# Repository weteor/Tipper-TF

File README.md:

# Tipper-TF
34 keys split unibody BLE keyboard. 

## Features

- low profile
- choc v1 w/ choc spacing
- angled hands
- splayed columns
- variable height on outer colum. Can be adjusted by a combination of pinheaders(1.27mm pitch, 1mm or 1.5mm height) + (at the moment) spacer pcbs.
- 1.54'' epaper display (Good Display GDEW0154M09)
- Bluetooth and USB connection 
- case files are supplied (stl, as well as freecad files)
- ZMK firmware support

## Want one?
All production files you need to build your own Tipper TF can be found [here](https://github.com/weteor/Tipper-TF/tree/main/production).

Please see the [build instruction](https://github.com/weteor/Tipper-TF/tree/main/production/build_instructions.md) for a more detailed listing of all things needed.

All PCBs come with SMT assembly files, so you can order them fully assembled. No need to solder another 50 diodes.

The files for the case are also provided. If you don't own a 3d printer, I've used JLCPCBs printing service (MJF nylon) and it turned out very good, so maybe take a look at that option.

### firmware 
The Tipper TF uses ZMK firmware.

The zmk driver for the display driver chip is not in the official repository yet, so you will have to use [my ZMK fork](https://github.com/weteor/zmk/tree/Tipper_TF_rev2) if you want to build a firmware locally.

If you prefer the github workflow, you can find the zmk config for the Tipper TF [here](https://github.com/weteor/Tipper_TF-Config). The config is already configured to pull ZMK from my fork, so you don't have to do anything further.

### some more pictures

## remarks
MKB keycaps work great on the Tipper, but I very much prefer the Chicago Steno caps by Pseudoku. He provides some nice SCAD files for those, you may find them in [his github](https://github.com/pseudoku/PseudoMakeMeKeyCapProfiles). He also sells them in his shop [www.asymplex.xyz](https://www.asymplex.xyz/).

### thanks for help and inspiration:
- [MangoIV](https://github.com/MangoIV/) and his [le-chiffre-ble](https://github.com/MangoIV/le_chiff_ble)
- [broom's](https://github.com/davidphilipbarr) [hypergolic](https://github.com/davidphilipbarr/hypergolic)
- [marv](https://github.com/MarvFPV) invaluable feedback and help with the case design

## the rest
Everything in this repository is free to use however you might see fit. If you want to support me and my projects, please consider linking back to this repository if you build/change/use anything. 

If you would like to send me a tip, you could do it [here](https://ko-fi.com/weteor) (Please don't feel like you have to).

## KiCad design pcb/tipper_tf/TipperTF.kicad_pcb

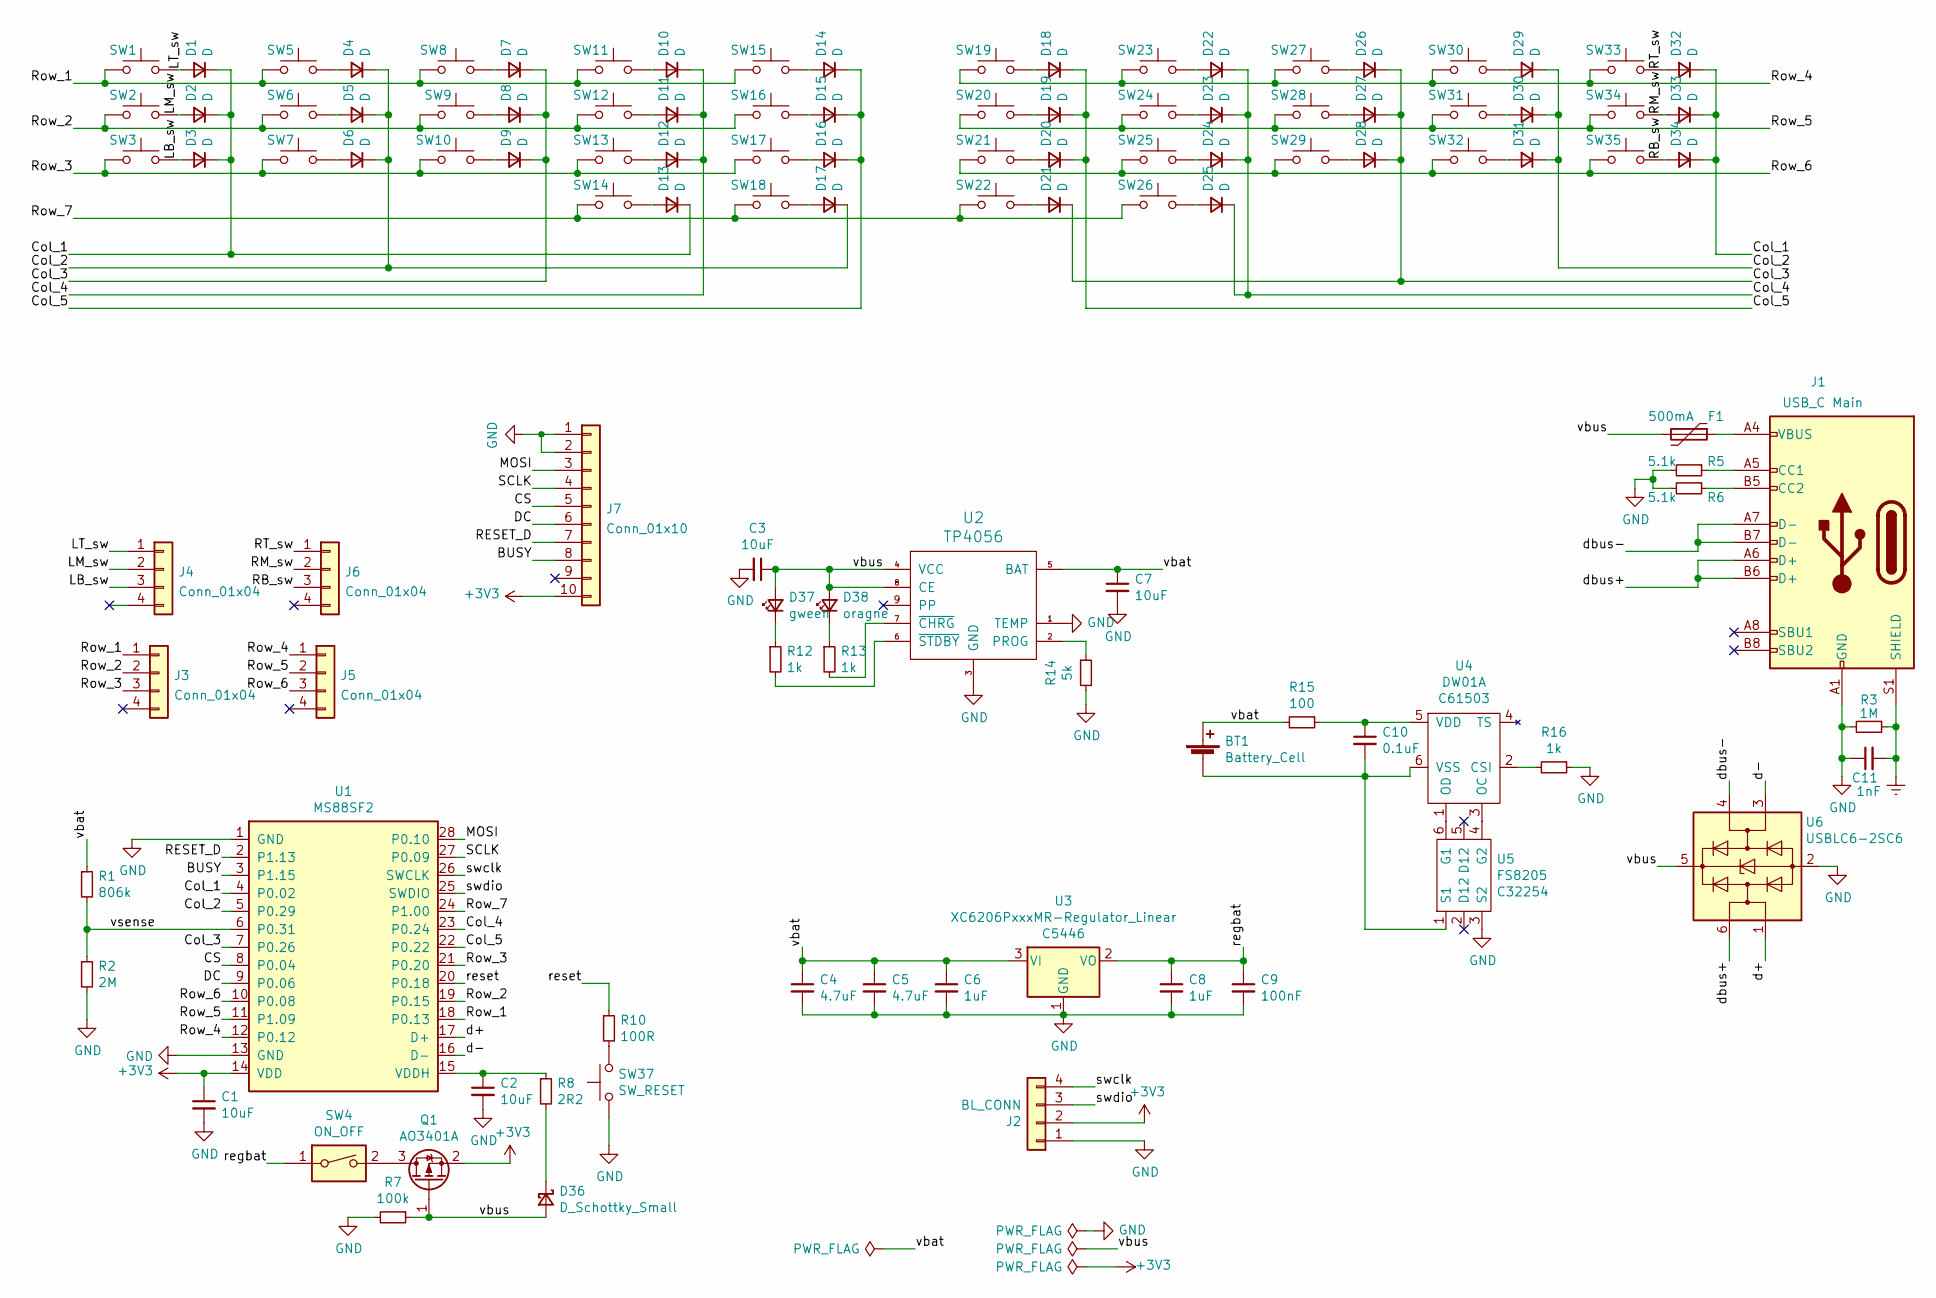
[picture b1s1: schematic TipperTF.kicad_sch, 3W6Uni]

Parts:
BT1: Battery_Cell; PinHeader_1x02_P2.54mm_Vertical
C1, C2, C3, C7: 10uF; C_0805_2012Metric
C4, C5: 4.7uF; C_0805_2012Metric
C6, C8: 1uF; C_0805_2012Metric
C9: 100nF; C_0805_2012Metric
C10: 0.1uF; C_0805_2012Metric
C11: 1nF; C_0805_2012Metric
D1, D2, D3, D4, D5, D6, D7, D8, D9, D10, D11, D12, D13, D14, D15, D16, D17, D18, D19, D20, D21, D22, D23, D24, D25, D26, D27, D28, D29, D30, D31, D32, D33, D34: D; D_SOD-123
D36: D_Schottky_Small; D_SOD-323_HandSoldering
D37: gween; D_0805_2012Metric
D38: oragne; D_0805_2012Metric
F1: 500mA; Fuse_1206_3216Metric
J1: USB_C Main; USB-C-12-Pin-MidMount
J2: BL_CONN; PinHeader_1x04_P2.54mm_Vertical
J3, J4, J5, J6: Conn_01x04; PinHeader_1x04_P1.27mm_Vertical
J7: Conn_01x10; FCC 1x10 - JUSHUO AFC01-S10FCA-00
Q1: AO3401A; SOT-23
R1: 806k; R_0805_2012Metric_Pad1.20x1.40mm_HandSolder
R2: 2M; R_0805_2012Metric_Pad1.20x1.40mm_HandSolder
R3: 1M; R_0805_2012Metric_Pad1.20x1.40mm_HandSolder
R5, R6: 5.1k; R_0805_2012Metric_Pad1.20x1.40mm_HandSolder
R7: 100k; R_0805_2012Metric_Pad1.20x1.40mm_HandSolder
R8: 2R2; R_0805_2012Metric_Pad1.20x1.40mm_HandSolder
R10: 100R; R_0805_2012Metric_Pad1.20x1.40mm_HandSolder
R12, R13, R16: 1k; R_0805_2012Metric_Pad1.20x1.40mm_HandSolder
R14: 5k; R_0805_2012Metric_Pad1.20x1.40mm_HandSolder
R15: 100; R_0805_2012Metric_Pad1.20x1.40mm_HandSolder
SW1, SW2, SW3, SW5, SW6, SW7, SW8, SW9, SW10, SW11, SW12, SW13, SW15, SW16, SW17, SW18, SW19, SW20, SW21, SW22, SW23, SW24, SW25, SW27, SW28, SW29, SW30, SW31, SW32, SW33, SW34, SW35: SW_Push; Kailh_Choc_1u
SW4: ON_OFF; K3-2380S-E1 On-on
SW14, SW26: SW_Push; Kailh_Choc_1.5u
SW37: SW_RESET; Micro_Push_Button_3x6x2.5mm
U1: MS88SF2; MINEW_MS88SF2
U2: TP4056; TP4056_SOP-8-PP
U3: XC6206PxxxMR-Regulator_Linear; SOT-23; LCSC C5446
U4: DW01A; SOT-23-6; LCSC C61503
U5: FS8205; SOT-23-6; LCSC C32254
U6: USBLC6-2SC6; SOT-23-6

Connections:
+3V3: C1.1, J2.2, J7.10, Q1.2 (S), U1.14 (VDD)
/BUSY: J7.8, U1.3 (P1.15)
/CS: J7.5, U1.8 (P0.04)
/Col_1: D1.1 (K), D2.1 (K), D3.1 (K), D13.1 (K), D32.1 (K), D33.1 (K), D34.1 (K), U1.4 (P0.02)
/Col_2: D4.1 (K), D5.1 (K), D6.1 (K), D17.1 (K), D29.1 (K), D30.1 (K), D31.1 (K), U1.5 (P0.29)
/Col_3: D7.1 (K), D8.1 (K), D9.1 (K), D21.1 (K), D26.1 (K), D27.1 (K), D28.1 (K), U1.7 (P0.26)
/Col_4: D10.1 (K), D11.1 (K), D12.1 (K), D22.1 (K), D23.1 (K), D24.1 (K), D25.1 (K), U1.23 (P0.24)
/Col_5: D14.1 (K), D15.1 (K), D16.1 (K), D18.1 (K), D19.1 (K), D20.1 (K), U1.22 (P0.22)
/DC: J7.6, U1.9 (P0.06)
/LB_sw: D3.2 (A), J4.3, SW3.2
/LM_sw: D2.2 (A), J4.2, SW2.2
/LT_sw: D1.2 (A), J4.1, SW1.2
/MOSI: J7.3, U1.28 (P0.10)
/RB_sw: D34.2 (A), J6.3, SW35.2
/RESET_D: J7.7, U1.2 (P1.13)
/RM_sw: D33.2 (A), J6.2, SW34.2
/RT_sw: D32.2 (A), J6.1, SW33.2
/Row_1: J3.1, SW1.1, SW5.1, SW8.1, SW11.1, SW15.1, U1.18 (P0.13)
/Row_2: J3.2, SW2.1, SW6.1, SW9.1, SW12.1, SW16.1, U1.19 (P0.15)
/Row_3: J3.3, SW3.1, SW7.1, SW10.1, SW13.1, SW17.1, U1.21 (P0.20)
/Row_4: J5.1, SW19.1, SW23.1, SW27.1, SW30.1, SW33.1, U1.12 (P0.12)
/Row_5: J5.2, SW20.1, SW24.1, SW28.1, SW31.1, SW34.1, U1.11 (P1.09)
/Row_6: J5.3, SW21.1, SW25.1, SW29.1, SW32.1, SW35.1, U1.10 (P0.08)
/Row_7: SW14.1, SW18.1, SW22.1, SW26.1, U1.24 (P1.00)
/SCLK: J7.4, U1.27 (P0.09)
/d+: U1.17 (D+), U6.1 (I/O1)
/d-: U1.16 (D-), U6.3 (I/O2)
/dbus+: J1.A6 (D+), J1.B6 (D+), U6.6 (I/O1)
/dbus-: J1.A7 (D-), J1.B7 (D-), U6.4 (I/O2)
/regbat: C8.1, C9.1, SW4.1, U3.2 (VO)
/reset: R10.1, U1.20 (P0.18)
/swclk: J2.4, U1.26 (SWCLK)
/swdio: J2.3, U1.25 (SWDIO)
/vbat: BT1.1 (+), C4.1, C5.1, C6.1, C7.1, R1.1, R15.2, U2.5 (BAT), U3.3 (VI)
/vbus: C3.1, D36.2 (A), D37.2 (A), D38.2 (A), F1.2, Q1.1 (G), R7.1, U2.4 (VCC), U2.8 (CE), U6.5 (VBUS)
/vsense: R1.2, R2.1, U1.6 (P0.31)
Earth: C11.2, J1.S1 (SHIELD), R3.1
GND: C1.2, C2.2, C3.2, C4.2, C5.2, C6.2, C7.2, C8.2, C9.2, C11.1, J1.A1 (GND), J1.A12 (GND), J1.B1 (GND), J1.B12 (GND), J2.1, J7.1, J7.2, R2.2, R3.2, R5.2, R6.2, R7.2, R14.2, R16.1, SW37.1, U1.1 (GND), U1.13 (GND), U2.1 (TEMP), U2.3 (GND), U3.1 (GND), U5.3 (S2), U6.2 (GND)
unnamed: BT1.2 (-), C10.2, U4.6 (VSS), U5.1 (S1)
unnamed: C2.1, R8.1, U1.15 (VDDH)
unnamed: C10.1, R15.1, U4.5 (VDD)
unnamed: D4.2 (A), SW5.2
unnamed: D5.2 (A), SW6.2
unnamed: D6.2 (A), SW7.2
unnamed: D7.2 (A), SW8.2
unnamed: D8.2 (A), SW9.2
unnamed: D9.2 (A), SW10.2
unnamed: D10.2 (A), SW11.2
unnamed: D11.2 (A), SW12.2
unnamed: D12.2 (A), SW13.2
unnamed: D13.2 (A), SW14.2
unnamed: D14.2 (A), SW15.2
unnamed: D15.2 (A), SW16.2
unnamed: D16.2 (A), SW17.2
unnamed: D17.2 (A), SW18.2
unnamed: D18.2 (A), SW19.2
unnamed: D19.2 (A), SW20.2
unnamed: D20.2 (A), SW21.2
unnamed: D21.2 (A), SW22.2
unnamed: D22.2 (A), SW23.2
unnamed: D23.2 (A), SW24.2
unnamed: D24.2 (A), SW25.2
unnamed: D25.2 (A), SW26.2
unnamed: D26.2 (A), SW27.2
unnamed: D27.2 (A), SW28.2
unnamed: D28.2 (A), SW29.2
unnamed: D29.2 (A), SW30.2
unnamed: D30.2 (A), SW31.2
unnamed: D31.2 (A), SW32.2
unnamed: D36.1 (K), R8.2
unnamed: D37.1 (K), R12.1
unnamed: D38.1 (K), R13.1
unnamed: F1.1, J1.A4 (VBUS), J1.A9 (VBUS), J1.B4 (VBUS), J1.B9 (VBUS)
unnamed: J1.A5 (CC1), R5.1
unnamed: J1.B5 (CC2), R6.1
unnamed: Q1.3 (D), SW4.2
unnamed: R10.2, SW37.2
unnamed: R12.2, U2.6 (~STDBY)
unnamed: R13.2, U2.7 (~CHRG)
unnamed: R14.1, U2.2 (PROG)
unnamed: R16.2, U4.2 (CSI)
unnamed: U4.1 (OD), U5.6 (G1)
unnamed: U4.3 (OC), U5.4 (G2)

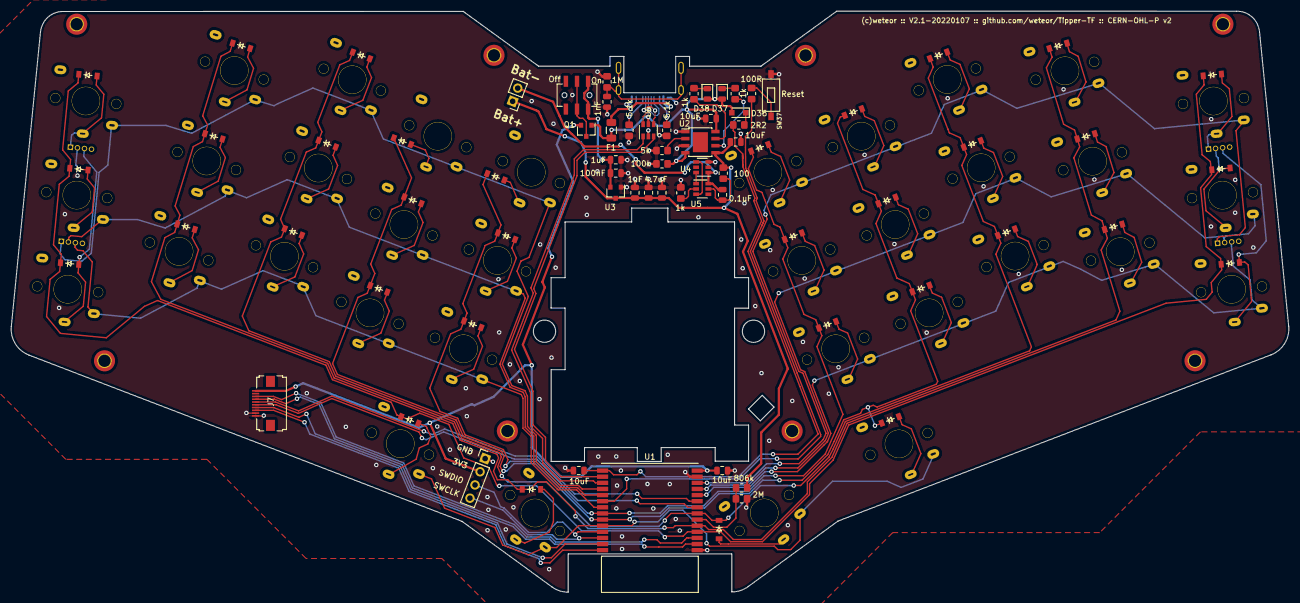
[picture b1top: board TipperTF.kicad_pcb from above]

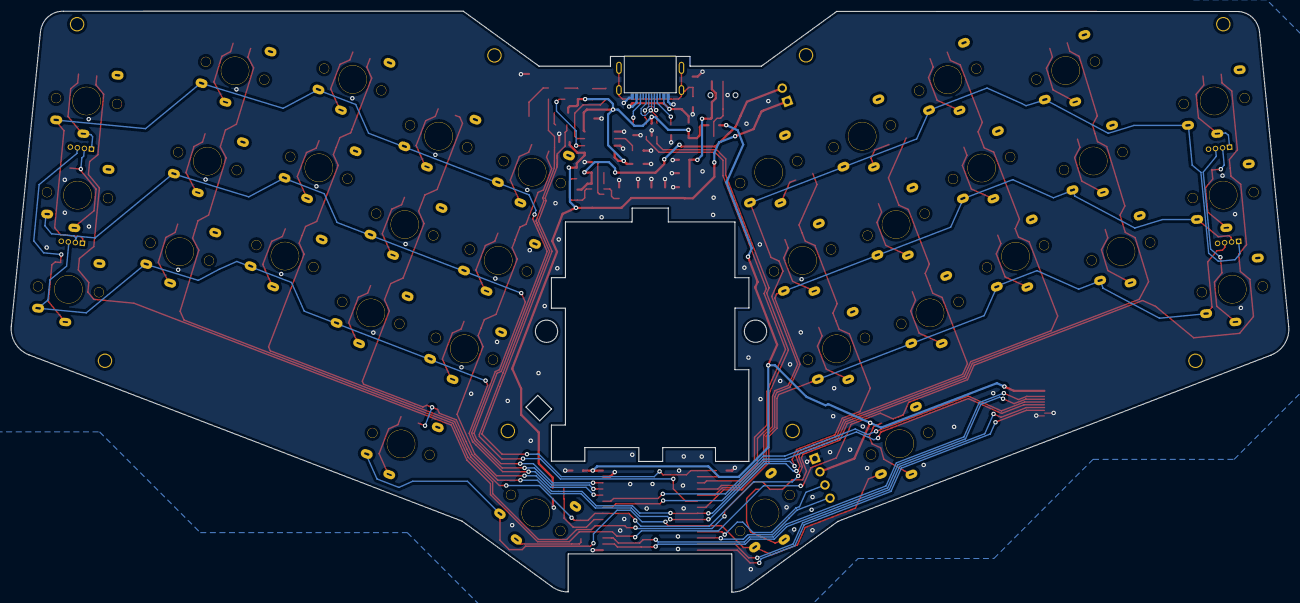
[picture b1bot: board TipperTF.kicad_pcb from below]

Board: 2 copper layers, 229.6 x 104.4 mm, 113 parts (39 on the bottom side), 83 nets.

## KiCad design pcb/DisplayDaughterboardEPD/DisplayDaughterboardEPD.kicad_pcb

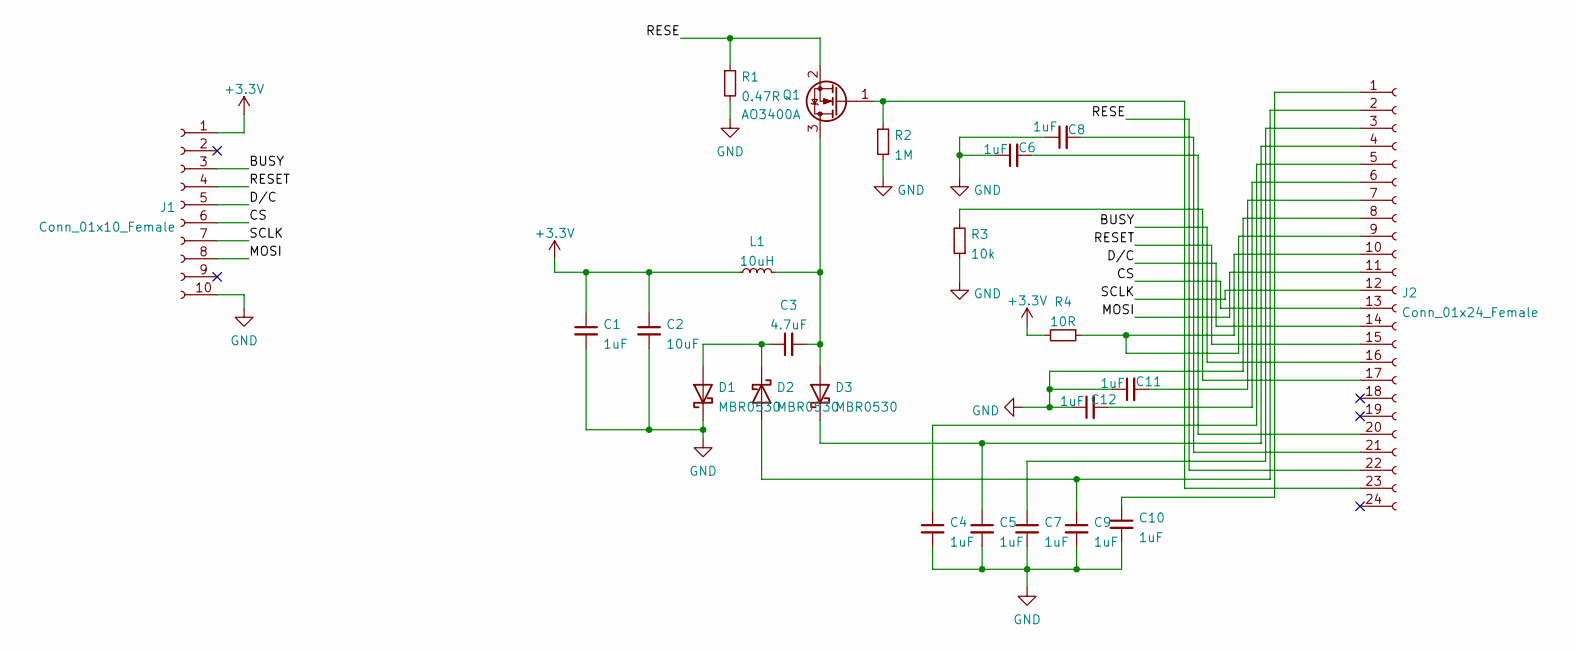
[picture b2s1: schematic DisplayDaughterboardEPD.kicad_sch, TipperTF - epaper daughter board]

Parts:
C1, C4, C5, C6, C7, C8, C9, C10, C11, C12: 1uF; C_0603_1608Metric
C2: 10uF; C_0603_1608Metric
C3: 4.7uF; C_0603_1608Metric
D1, D2, D3: MBR0530; D_SOD-123
J1: Conn_01x10_Female; FCC 1x10 - JUSHUO AFC01-S10FCA-00
J2: Conn_01x24_Female; TE_2-1734839-4_1x24-1MP_P0.5mm_Horizontal
L1: 10uH; L_1210_3225Metric
Q1: AO3400A; SOT-23
R1: 0.47R; R_0603_1608Metric
R2: 1M; R_0603_1608Metric
R3: 10k; R_0603_1608Metric
R4: 10R; R_0603_1608Metric

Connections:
+3V3: C1.1, C2.1, J1.1, L1.1, R4.2
/BUSY: J1.3, J2.16
/CS: J1.6, J2.13
/D/C: J1.5, J2.14
/MOSI: J1.8, J2.11
/RESE: J2.22, Q1.2 (S), R1.1
/RESET: J1.4, J2.15
/SCLK: J1.7, J2.12
GND: C1.2, C2.2, C4.2, C5.2, C6.1, C7.2, C8.1, C9.2, C10.2, C11.1, C12.1, D1.1 (K), J1.10, J2.8, R1.2, R2.1, R3.1
unnamed: C3.1, D1.2 (A), D2.1 (K)
unnamed: C3.2, D3.2 (A), L1.2, Q1.3 (D)
unnamed: C4.1, J2.5
unnamed: C5.1, D3.1 (K), J2.4
unnamed: C6.2, J2.20
unnamed: C7.1, J2.3
unnamed: C8.2, J2.21
unnamed: C9.1, D2.2 (A), J2.2
unnamed: C10.1, J2.1
unnamed: C11.2, J2.7
unnamed: C12.2, J2.6
unnamed: J2.9, J2.10, R4.1
unnamed: J2.17, R3.2
unnamed: J2.23, Q1.1 (G), R2.2

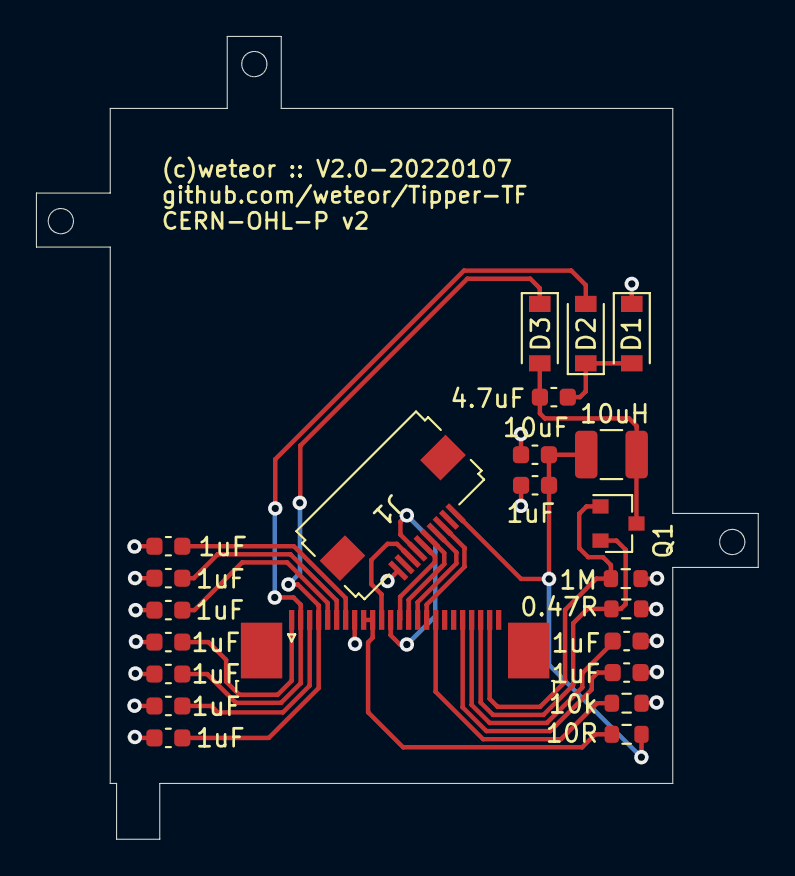
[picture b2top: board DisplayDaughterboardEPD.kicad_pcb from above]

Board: 2 copper layers, 40.1 x 44.6 mm, 23 parts (0 on the bottom side), 23 nets.

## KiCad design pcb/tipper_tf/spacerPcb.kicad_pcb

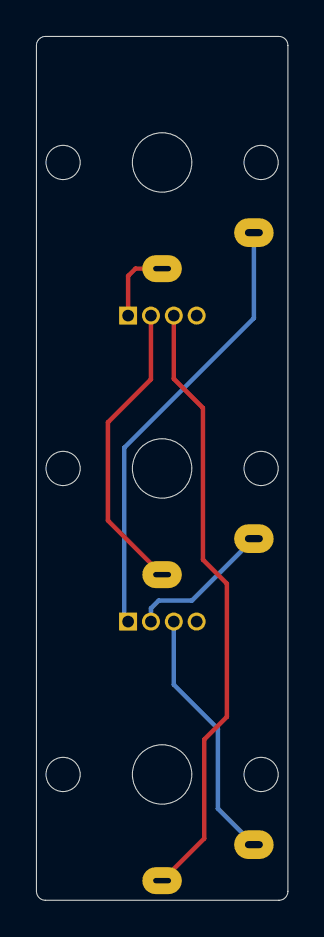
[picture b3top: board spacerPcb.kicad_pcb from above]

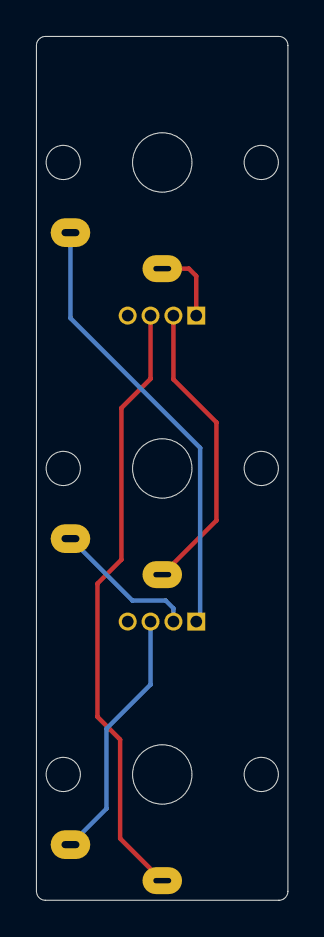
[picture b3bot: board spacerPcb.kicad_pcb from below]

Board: 2 copper layers, 14.0 x 48.0 mm, 5 parts (5 on the bottom side), 6 nets.

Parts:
J3, J4: Conn_01x04; PinHeader_1x04_P1.27mm_Vertical
SW1, SW2, SW3: SW_Push; Kailh_Choc_1u

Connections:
/LB_sw: J4.3, SW3.2
/LM_sw: J4.2, SW2.2
/LT_sw: J4.1, SW1.2
/Row1: J3.1, SW1.1
/Row2: J3.2, SW2.1
/Row3: J3.3, SW3.1

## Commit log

2021-08-18 initial (sort of) cadquery sources
2021-08-18 encoder docs
2021-08-18 add LICENSE
2021-08-20 restructure GeneratePlate to allow a angled columns clean up and rewriting to us Locations
2021-08-20 changed some angles and distances
2021-08-23 new case function, shorter, using locations
2021-08-25 change config. add screw holes and case bottom
2021-08-26 first version fix: case, pcb
2021-08-26 generated dxf and stl files for v1
2021-08-26 add initial kicad project and library
2021-08-28 fix bug in height and cleaning up configs
2021-08-28 new stl dxf files with usbport opening
2021-08-28 add rotary encoder to lib.WIP PCB
2021-09-02 add space for battery fix holes and placements
2021-09-02 pcb routed
2021-09-10 case add notch at thumbs
2021-09-10 make pcb ready for manufacturing, add backplate
2021-09-11 new version case
2021-09-11 angled case
2021-09-13 new case angle
2021-09-22 prototype pcb added
2021-09-22 add pcb gerbers and case stl/step
2021-09-22 cleanup
2021-09-22 add prototype pictures
2021-09-24 add stls and new images
2021-09-24 new images
2021-10-08 test for display
2021-10-08 change board outline to match case
2021-10-12 pcb almost ready
2021-10-19 change: case lower Angle and display cutout
2021-10-19 fix main pcb, new matrix layout, display support, new screwhole positions
2021-10-19 add Display daughterboard
2021-10-19 change: spacer and backside pcbs changed to reflect changes in case and main pcb
2021-11-09 daughterboard update for prod rev2
2021-11-09 pcb update rev2 prod.
2021-11-09 move prod data from rev 1
2021-11-09 change display board to allow for more room above connectors
2021-11-09 add production data for rev2 proto
2021-11-09 add freecad sources for case
2021-11-09 move rev 1 to own folder
2021-11-09 add proto images rev2
2021-12-04 add images of Rev2 proto
2021-12-04 new img
2021-12-04 right image this time
2021-12-04 rem image
2021-12-04 new top image
2021-12-05 add layout svg
2021-12-05 new layout svg
2021-12-06 new, hopefully corrected version of displayboard
2021-12-06 new production files for display
2021-12-06 unsaved changes
2021-12-28 fix case. reset Button, display cutout
2021-12-29 readme for main pcb production files
2021-12-29 readme for display daughterboard
2021-12-29 readme for spacer pcbs
2021-12-29 add build instructions
2021-12-29 Update main readme
2021-12-29 replaced not in stock Bom components
2021-12-29 replaced non in stock component in Bom for Display board
2022-01-02 add usb connector to build instructions
2022-01-12 fixed bottom case to account for switch legs
2022-01-12 add license print to front silkscreen
2022-01-12 newest revision of pcb, adds support for choc V2 (WITH CHOC SPACING) and tighening the holes for V1
2022-01-12 add production files from latest GB
2022-01-12 add missing production data
2022-01-12 add library footprints for combined switches
2022-01-30 case: better screw placement, remove small features for better fdm
2022-02-08 add bottom stl w/ sacrificial planes
2022-02-08 new version of fdm bottom

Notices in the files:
pcb/DisplayDaughterboardEPD/DisplayDaughterboardEPD.kicad_pcb:
CERN-OHL-P v2
pcb/DisplayDaughterboardEPD/DisplayDaughterboardEPD.kicad_sch:
Licensed under CERN-OHL-P v2
pcb/tipper_tf/TipperTF.kicad_pcb:
(c)weteor :: V2.1-20220107 :: github.com/weteor/Tipper-TF :: CERN-OHL-P v2
